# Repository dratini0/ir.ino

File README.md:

# IR.ino

IR.ino is a small device that is meant to capture and replay infrared signals coming from remote controls.

Planned features:
* Removing dependance on arduino library
* LIRC support

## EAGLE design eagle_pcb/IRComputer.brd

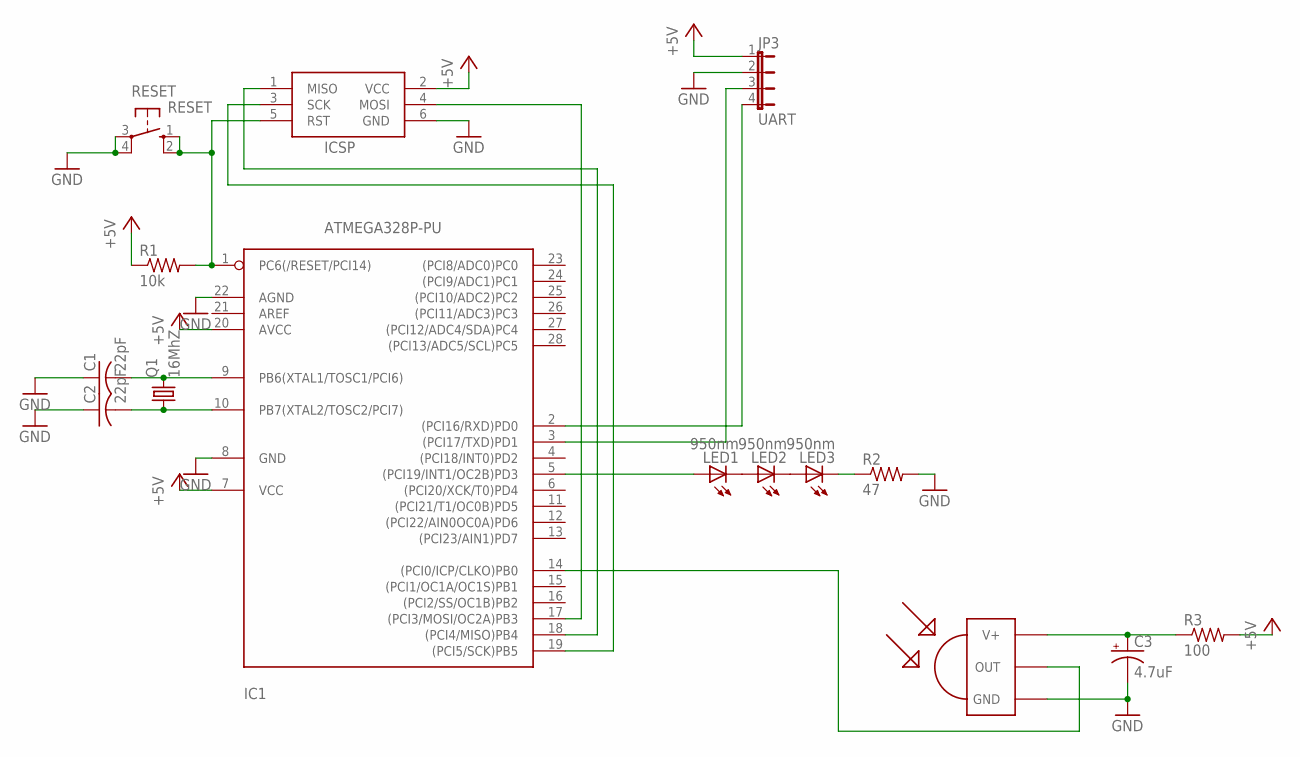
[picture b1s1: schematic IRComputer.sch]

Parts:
C1, C2: 22pF; C025-024X044
C3: 4.7uF; E1,8-4
IC1: ATMEGA328P-PU; DIL28-3
ICSP: AVRISP-6; AVRISP
JP3: UART; JP4
LED1, LED2, LED3: 950nm; LED5MM
Q1: 16MhZ; HC49/S
R1: 10k; 0204/7
R2: 47; 0204/7
R3: 100; 0204/7
RESET: RESET; B3F-10XX
U$1: TSOP1838; TSOP18XX

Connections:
+5V: IC1.7 (VCC), IC1.20 (AVCC), ICSP.2 (VCC), JP3.1, R1.1, R3.2
GND: C1.1, C2.1, C3.-, IC1.8 (GND), IC1.22 (AGND), ICSP.6 (GND), JP3.2, R2.2, RESET.3, RESET.4 (P1), U$1.GND
unnamed: C1.2, IC1.9 (PB6(XTAL1/TOSC1/PCI6)), Q1.2
unnamed: C2.2, IC1.10 (PB7(XTAL2/TOSC2/PCI7)), Q1.1
unnamed: IC1.14 ((PCI0/ICP/CLKO)PB0), U$1.OUT
unnamed: C3.+, R3.1, U$1.VCC (V+)
unnamed: IC1.3 ((PCI17/TXD)PD1), JP3.3
unnamed: IC1.2 ((PCI16/RXD)PD0), JP3.4
unnamed: IC1.5 ((PCI19/INT1/OC2B)PD3), LED1.A
unnamed: IC1.17 ((PCI3/MOSI/OC2A)PB3), ICSP.4 (MOSI)
unnamed: IC1.18 ((PCI4/MISO)PB4), ICSP.1 (MISO)
unnamed: IC1.19 ((PCI5/SCK)PB5), ICSP.3 (SCK)
unnamed: LED2.K (C), LED3.A
unnamed: LED3.K (C), R2.1
unnamed: LED1.K (C), LED2.A
unnamed: IC1.1 (PC6(/RESET/PCI14)), ICSP.5 (RST), R1.2, RESET.1 (S), RESET.2 (S1)

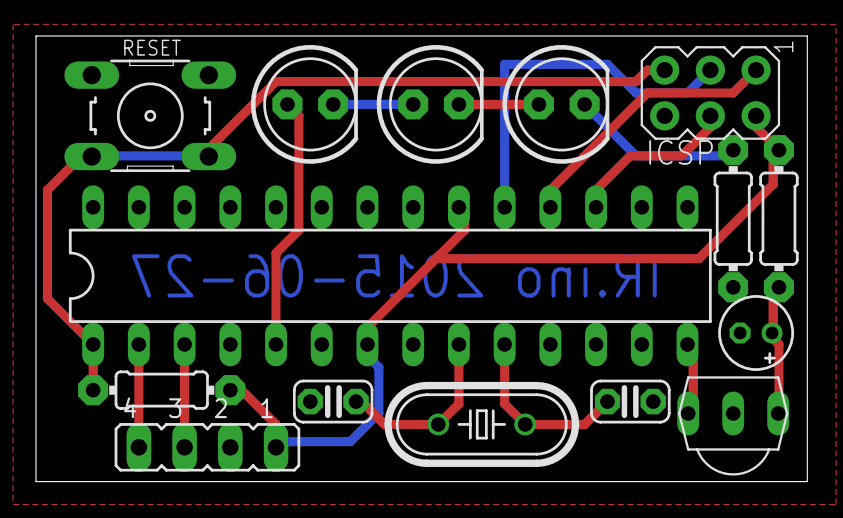
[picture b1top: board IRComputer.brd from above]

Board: 2 copper layers, 42.9 x 24.8 mm, 15 parts (0 on the bottom side), 16 nets.
